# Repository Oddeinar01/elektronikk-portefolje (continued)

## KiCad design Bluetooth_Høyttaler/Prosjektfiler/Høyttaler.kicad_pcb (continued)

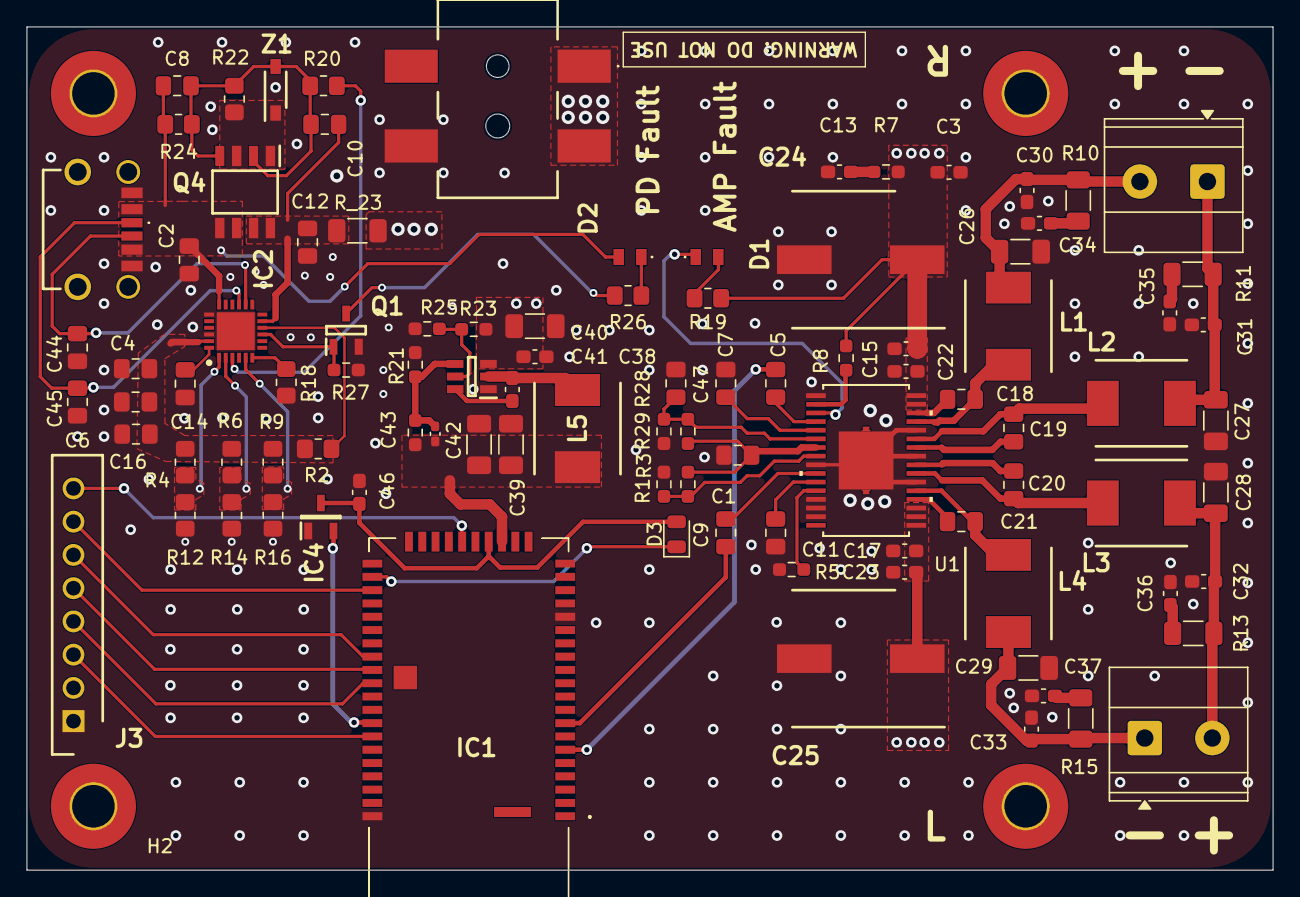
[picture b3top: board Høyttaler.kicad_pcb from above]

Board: 4 copper layers, 93.7 x 63.4 mm, 102 parts (0 on the bottom side), 63 nets.

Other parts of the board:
C46: 0.1uF; C_0603_1608Metric_Pad1.08x0.95mm_HandSolder
D3: KT-0805B; D_0805_2012Metric
IC1: BM83SM1-00AA; BM83SM100AA
IC4: TLV803SDBZR; SOT95P237X112-3N

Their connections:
3V3BUCK: IC1.23 (BAT_IN); also elsewhere on the board
/BT Module/RST_N: IC1.43 (RST_N), IC4.2 (~RESET)
/BT Module/SYS_PWR: C46.1, D3.2 (A), IC1.24 (SYS_PWR), IC4.3 (VDD)
BT_NEXT: IC1.44 (P0_1); also elsewhere on the board
BT_PLAY_PAUSE: IC1.33 (P0_2); also elsewhere on the board
BT_PREV: IC1.38 (P0_3); also elsewhere on the board
BT_PRW: IC1.26 (PWR_(MFB)); also elsewhere on the board
BT_VOL+: IC1.39 (P2_7); also elsewhere on the board
BT_VOL-: IC1.40 (P0_5); also elsewhere on the board
GND: C46.2, IC1.16 (GND_1), IC1.50 (GND_2), IC4.1 (GND); also elsewhere on the board
LINP: IC1.8 (AOHPL); also elsewhere on the board
unnamed: D3.1 (K), IC1.32 (LED1)
RINP: IC1.6 (AOHPR); also elsewhere on the board

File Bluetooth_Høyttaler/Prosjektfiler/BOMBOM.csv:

"Reference","Qty","Value","Footprint","Manufacturer_Name","Manufacturer_Part_Number","Mouser_Part_Number"
"C1,C47","2","1uF","Capacitor_SMD:C_0805_2012Metric_Pad1.18x1.45mm_HandSolder","KYOCERA AVX","KGM21AR71C105JU","581-KGM21AR71C105JU"
"C2,C12","2","10uF","Capacitor_SMD:C_0805_2012Metric_Pad1.18x1.45mm_HandSolder","TDK","C2012X5R1V106M085AC","810-C2012X5R1V106M0C"
"C3,C34,C35,C36,C37","5","10nF","Capacitor_SMD:C_0603_1608Metric_Pad1.08x0.95mm_HandSolder","Murata Electronics","GCM188R71H103KA37J","81-GCM188R71H103KA7J"
"C4,C6","2","0.1uF","Capacitor_SMD:C_0805_2012Metric_Pad1.18x1.45mm_HandSolder","YAGEO","AC0805KRX7R7BB104","603-AC805KRX7R7BB104"
"C5,C7,C9,C11","4","3.3uF","Capacitor_SMD:C_0805_2012Metric_Pad1.18x1.45mm_HandSolder","Samsung Electro-Mechanics","CL21B335KLB6PNE","187-CL21B335KLB6PNE"
"C8,C10,C14,C16","4","1uF","Capacitor_SMD:C_0805_2012Metric_Pad1.18x1.45mm_HandSolder","TDK","CGA4J3X7R1V105K125AB","810-CGA4J3X7R1V105K"
"C13,C22,C23","3","100nF","Capacitor_SMD:C_0603_1608Metric_Pad1.08x0.95mm_HandSolder","YAGEO","CC0603KRX7R8BB104","603-CC603KRX7R8BB104"
"C15,C17,C30,C31,C32,C33","6","1nF","Capacitor_SMD:C_0603_1608Metric_Pad1.08x0.95mm_HandSolder","Walsin","0603N102K500CT","791-0603N102K500CT"
"C18,C19,C20,C21","4","220nF","Capacitor_SMD:C_0805_2012Metric_Pad1.18x1.45mm_HandSolder","KYOCERA AVX","KAM21KR71E224KU","581-KAM21KR71E224KU"
"C24,C25","2","220uF","A768MS227M1GLAS022 POLYMER CAPACITOR:CAPAE1030X1270N","KEMET","A768MS227M1GLAS022","80-A768MS227M1GLAS22"
"C26,C27,C28,C29","4","680nF","Capacitor_SMD:C_1206_3216Metric_Pad1.33x1.80mm_HandSolder","TDK","CGA5L2X7R1H684K160AA","810-CGA5L2X7R1H684K"
"C38,C41,C46","3","0.1uF","Capacitor_SMD:C_0603_1608Metric_Pad1.08x0.95mm_HandSolder","Würth Elektronik","885012207072","710-885012207072"
"C39,C42","2","22uF","Capacitor_SMD:C_1206_3216Metric_Pad1.33x1.80mm_HandSolder","Walsin","1206X226M160CT","791-1206X226M160CT"
"C40","1","10uF","Capacitor_SMD:C_1206_3216Metric_Pad1.33x1.80mm_HandSolder","TAIYO YUDEN","MLAST32NSB5106MTNA01","963-MLAST32NSB5106MT"
"C43","1","47pF","Capacitor_SMD:C_0402_1005Metric_Pad0.74x0.62mm_HandSolder","KEMET","C0402C470J5GAC7411","80-C0402C470J5G7411"
"C44,C45","2","390pF","Capacitor_SMD:C_0805_2012Metric_Pad1.18x1.45mm_HandSolder","FH (Guangdong Fenghua Advanced Tech)","0805CG391J500NT",""
"D1,D2","2","C84256","my_footprints:NCD0805R1","NATIONSTAR","NCD0805R1",""
"D3","1","KT-0805B","Diode_SMD:D_0805_2012Metric","","KT-0805B",""
"IC1","1","BM83SM1-00AB","BM83SM1-00AB:BM83SM100AA","Microchip","BM83SM1-00AB","579-BM83SM1-00AB"
"IC2","1","CYPD3177-24LQXQ","CYPD3177-24LQXQ:QFN50P400X400X60-25N-D","Infineon","CYPD3177-24LQXQ","727-CYPD3177-24LQXQ"
"IC3","1","TPS54302DDCT","TPS54302DDCT:SOT95P280X110-6N","Texas Instruments","TPS54302DDCT","595-TPS54302DDCT"
"IC4","1","TLV803SDBZR","my_footprints:SOT95P237X112-3N","Texas Instruments","TLV803SDBZR",""
"J1","1","2479774-1","2479774-1 USB_C:24797741","TE Connectivity","2479774-1","571-2479774-1"
"J2","1","PJ-002AH-SMT-TR","my_footprints:PJ002AHSMTTR","Same Sky","PJ-002AH-SMT-TR",""
"J3","1","B8B-EH-A_LF__SN_","SHDR8W64P0X250_1X8_2250X380X600P","JST (JAPAN SOLDERLESS TERMINALS)","B8B-EH-A(LF)(SN)",""
"L1,L2,L3,L4","4","10uH","my_footprints:INDPM6965X300N","VIshay","IHLP2525CZER100MA1","C511066"
"L5","1","6.8uH","my_footprints:INDPM6965X300N","Vishay","IHLP2525CZER6R8M8A","70-IHLP2525CZR6R8M8A"
"LEFT1,RIGHT1","2","1715721","TerminalBlock_Phoenix:TerminalBlock_Phoenix_MKDS-1,5-2-5.08_1x02_P5.08mm_Horizontal","","1715721",""
"Q1","1","AO3400A","my_footprints:SOT95P280X125-3N","Alpha & Omega Semiconductors","AO3400A",""
"Q4","1","IRF9358TRPBF","IRF9358TRPBF:SOIC127P600X175-8N","Infineon","IRF9358TRPBF","942-IRF9358TRPBF"
"R1,R5,R8,R28","4","100k","Resistor_SMD:R_0603_1608Metric_Pad0.98x0.95mm_HandSolder","YAGEO","SR0603FR-07100KL","603-SR0603FR-07100KL"
"R2","1","49.9k","Resistor_SMD:R_0805_2012Metric_Pad1.20x1.40mm_HandSolder","YAGEO","AF0805FR-0749K9L","603-AF0805FR-0749K9L"
"R3","1","20k","Resistor_SMD:R_0603_1608Metric_Pad0.98x0.95mm_HandSolder","YAGEO","RE0603FRE0720KL","603-RE0603FRE0720KL"
"R4,R6,R9,R12,R14,R16,R18","7","5.1K","Resistor_SMD:R_0805_2012Metric_Pad1.20x1.40mm_HandSolder","YAGEO","RC0805FR-075K1L","603-RC0805FR-075K1L"
"R7","1","33R","Resistor_SMD:R_0603_1608Metric_Pad0.98x0.95mm_HandSolder","YAGEO","AF0603JR-0733RL","603-AF0603JR-0733RL"
"R10,R11,R13,R15","4","3.3R","Resistor_SMD:R_1206_3216Metric_Pad1.30x1.75mm_HandSolder","Panasonic Industry","ERJ-UP8F3R30V","667-ERJ-UP8F3R30V"
"R17,R27","2","100k","Resistor_SMD:R_0603_1608Metric_Pad0.98x0.95mm_HandSolder","Vishay","RCA0603100KFKEC","71-RCA0603100KFKEC"
"R19","1","6.8k","Resistor_SMD:R_0805_2012Metric_Pad1.20x1.40mm_HandSolder","Panasonic Industry","ERA-6AED682V","667-ERA-6AED682V"
"R20,R26","2","1k","Resistor_SMD:R_0805_2012Metric_Pad1.20x1.40mm_HandSolder","Ohmite","AS08J1001ET","588-AS08J1001ET"
"R21","1","22.1k","Resistor_SMD:R_0603_1608Metric_Pad0.98x0.95mm_HandSolder","Bourns","CR0603-FX-2212ELF","652-CR0603FX-2212ELF"
"R22","1","49.9K","Resistor_SMD:R_0805_2012Metric_Pad1.20x1.40mm_HandSolder","YAGEO","AF0805FR-0749K9L","603-AF0805FR-0749K9L"
"R23","1","511k","Resistor_SMD:R_0603_1608Metric_Pad0.98x0.95mm_HandSolder","Bourns","CR0603-FX-5113ELF","652-CR0603FX-5113ELF"
"R24","1","10k","Resistor_SMD:R_0805_2012Metric_Pad1.20x1.40mm_HandSolder","Vishay","CRCW080510K0JNEA","71-CRCW0805J-10K-E3"
"R25","1","105k","Resistor_SMD:R_0603_1608Metric_Pad0.98x0.95mm_HandSolder","Panasonic","ERJ-3EKF1053V","667-ERJ-3EKF1053V"
"R29","1","130k","Resistor_SMD:R_0603_1608Metric_Pad0.98x0.95mm_HandSolder","FOJAN","FRC0603F1303TS",""
"R_23","1","0","Resistor_SMD:R_1206_3216Metric_Pad1.30x1.75mm_HandSolder","Bourns","CRF1206-J/-000ELF","652-CRF1206-J-000ELF"
"U1","1","TPA3129D2DAPR","footprints:DAP32_4P36X4P11_TEX","Texas Instruments","TPA3129D2DAPR","595-TPA3129D2DAPR"
"Z1","1","MMSZ10T1G","MMSZ10T1G:SOD3716X135N","onsemi","MMSZ10T1G","863-MMSZ10T1G"
